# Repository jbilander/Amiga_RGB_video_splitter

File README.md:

# Amiga_RGB_video_splitter
Extend your amiga RGB video signal to two display units - screens, monitors, etc, simultaneously

BOM Rev. C
---------
Reference  | Name/Value   | Package/Footprint | Notes
-|-|-|-|
U1 | THS7374IPWR | TSSOP-14_4.4x5mm_P0.65mm | [THS7374IPWR](https://www.mouser.com/ProductDetail/595-THS7374IPWR)
U2 | 74HCT2G17 | TSOP-6_1.65x3.05mm_P0.95mm | [HCT2G17GV125](https://www.mouser.com/ProductDetail/771-HCT2G17GV125)
U3 | 74HCT2G14 | TSOP-6_1.65x3.05mm_P0.95mm | [HCT2G14GV125](https://www.mouser.com/ProductDetail/771-HCT2G14GV125)
U4 | 74LVC1GX04GV X-TAL DRIVER | TSOP-6_1.65x3.05mm_P0.95mm | [LVC1GX04GV125](https://www.mouser.com/ProductDetail/771-LVC1GX04GV125)
Y1 | 18pF Crystal 28.6363 MHz (NTSC) or 28.375 MHz (PAL) | 3.2 mm x 2.5 mm | [ECS-286.3-18-33-JEM-TR](https://www.mouser.com/ProductDetail/520-286.3-18-33-JEMT) (NTSC)<br /> [ABM8-28.375MHZ-B2-T](https://www.mouser.com/ProductDetail/815-ABM8-28.375-B2-T) (PAL)
J1 | D-SUB DB23| DB23_Female-Connector | [Female 23 PIN DB23](https://www.aliexpress.com/item/1005007020706331.html)
J2 | DSUB-15-HD | HD_Female_Horizontal | [VGA connector](https://www.aliexpress.com/item/1005007383371077.html)
J3 | 9 Pin Mini Din Connector | Right Angle TH Mini Circular DIN Receptacle | [9pin Mini Din](https://www.aliexpress.com/item/1005005737270650.html)
J4 | PJ-320A | DIP 3.5mm Headphone Audio Socket 4Pins Audio interface | [PJ-320A](https://www.aliexpress.com/item/4000661212458.html)
J5 | MSK12D19 | 3Pin Slide Toggle Switch Pitch_2.5mm | [MSK12D19 SMD](https://www.aliexpress.com/item/1005006482584650.html)
J6 | MSK12D19 | 3Pin Slide Toggle Switch Pitch_2.5mm | [MSK12D19 SMD](https://www.aliexpress.com/item/1005006482584650.html)
J7 | Right angle Single-Pin Header | 0.64 mm square pin angled | pin for a flylead back to switchable Agnus pin 41 (or its pad on motherboard, e.g. JP4 on A500 Rev.6A)
JP1 | Solder_Jumper | | Solder Jumper for setting above pin (J7) to either /XCLKEN or OE-signal (inverted /XCLKEN signal).
C1 | 100uF Radial Pitch_2.5mm | Capacitor TH Radial_D5.0mm_P2.50mm | e.g. <br />[ECA-1AM101](https://www.mouser.com/ProductDetail/667-ECE-A0JKA101I) <br />[ECE-A0JKA101I](https://www.mouser.com/ProductDetail/667-ECA-1AM101) <br />Bend down flush to board before soldering
C2-C6 | Ceramic Capacitor 0.1uF = 100nF | 0805 | e.g. [CL21B104KACNFNC](https://www.mouser.com/ProductDetail/187-CL21B104KACNFNC)
C7-C8 | Multilayer Ceramic Capacitors MLCC - 32pF | 0603 | [06031A320FAT2A ](https://www.mouser.com/ProductDetail/581-06031A320FAT2A) for oscillator circuit
RN1-RN2 | 75 Ω RES ARRAY 4 Resistors | 1206 | [CAT16-75R0F4LF](https://www.mouser.com/ProductDetail/652-CAT16-75R0F4LF)
R1 | 330 Ω | 1206 | Series resistor on C-sync line
R2-R4 | 10k Ω | 1206  
R5 | Resistor 2.2M Ω | 0603 | Resistor in oscillator-circuit
R6 | Resistor 1k Ω | 0603 | Resistor in oscillator-circuit
R7 | Resistor 150 Ω | 1206 | Damping resistor for XCLK out to minimize reflections and ringing
Housing | 2 x Plastic Shell Cover | For DB23/DB25 plug | [Aliexpress](https://www.aliexpress.com/item/1005004717091904.html)
4 x PinHeader | PinHeader Board Weight/Level Support | 3-pin 2.54 mm pitch single row | Move the plastic guard to leave ~7.5 mm of pin before soldering in order to hold board in perfect level inside the housing

***

***

If you use jumper-wire from JP1-pin then you bridge it either with the left pad or the right pad depending on your setup:

    1. Motherboard has PAL oscillator and Adapter has NTSC oscillator = bridge JP1-pin with XCLKEN-pad (PAD 1)
    2. Motherboard has NTSC oscillator and Adapter has PAL oscillator = bridge JP1-pin with OE-pad (PAD 3)

Please note, using a jumper-wire is completely optional, You can switch ECS Agnus in Early Startup menu or with software such as Degrader and then you only control the external XLCK-crystal enable or disable via the switch on the adaptor. However it can be more convenient to have both tasks controlled from one single switch, hence connecting a jumper-wire.

***

<br />

Suitable SCART-lead to use with the adapter (originally for the SEGA Mega Drive 2, (Genesis 2) with AC coupling inside) <br />
https://www.aliexpress.com/item/1005007360209844.html

***

<br />

<br />

<br />

<br />
Filter OFF vs. Filter ON<br />
With the THS7374's filter activated you can clearly see that the vertical jailbars are gone (right picture).

***

When ordering from JLCPCB select:

Specify Layer Sequence: Yes

    L1(Top layer):    F_Cu.gbr
    L2(Inner layer1): GND_Cu.gbr
    L3(Inner layer2): VCC_Cu.gbr
    L4(Bottom layer): B_Cu.gbr

Remove Order Number: 

    Specify a location

This will notify JLC where to put the order number, they will replace the "JLCJLCJLCJLC" silkscreen label.

***

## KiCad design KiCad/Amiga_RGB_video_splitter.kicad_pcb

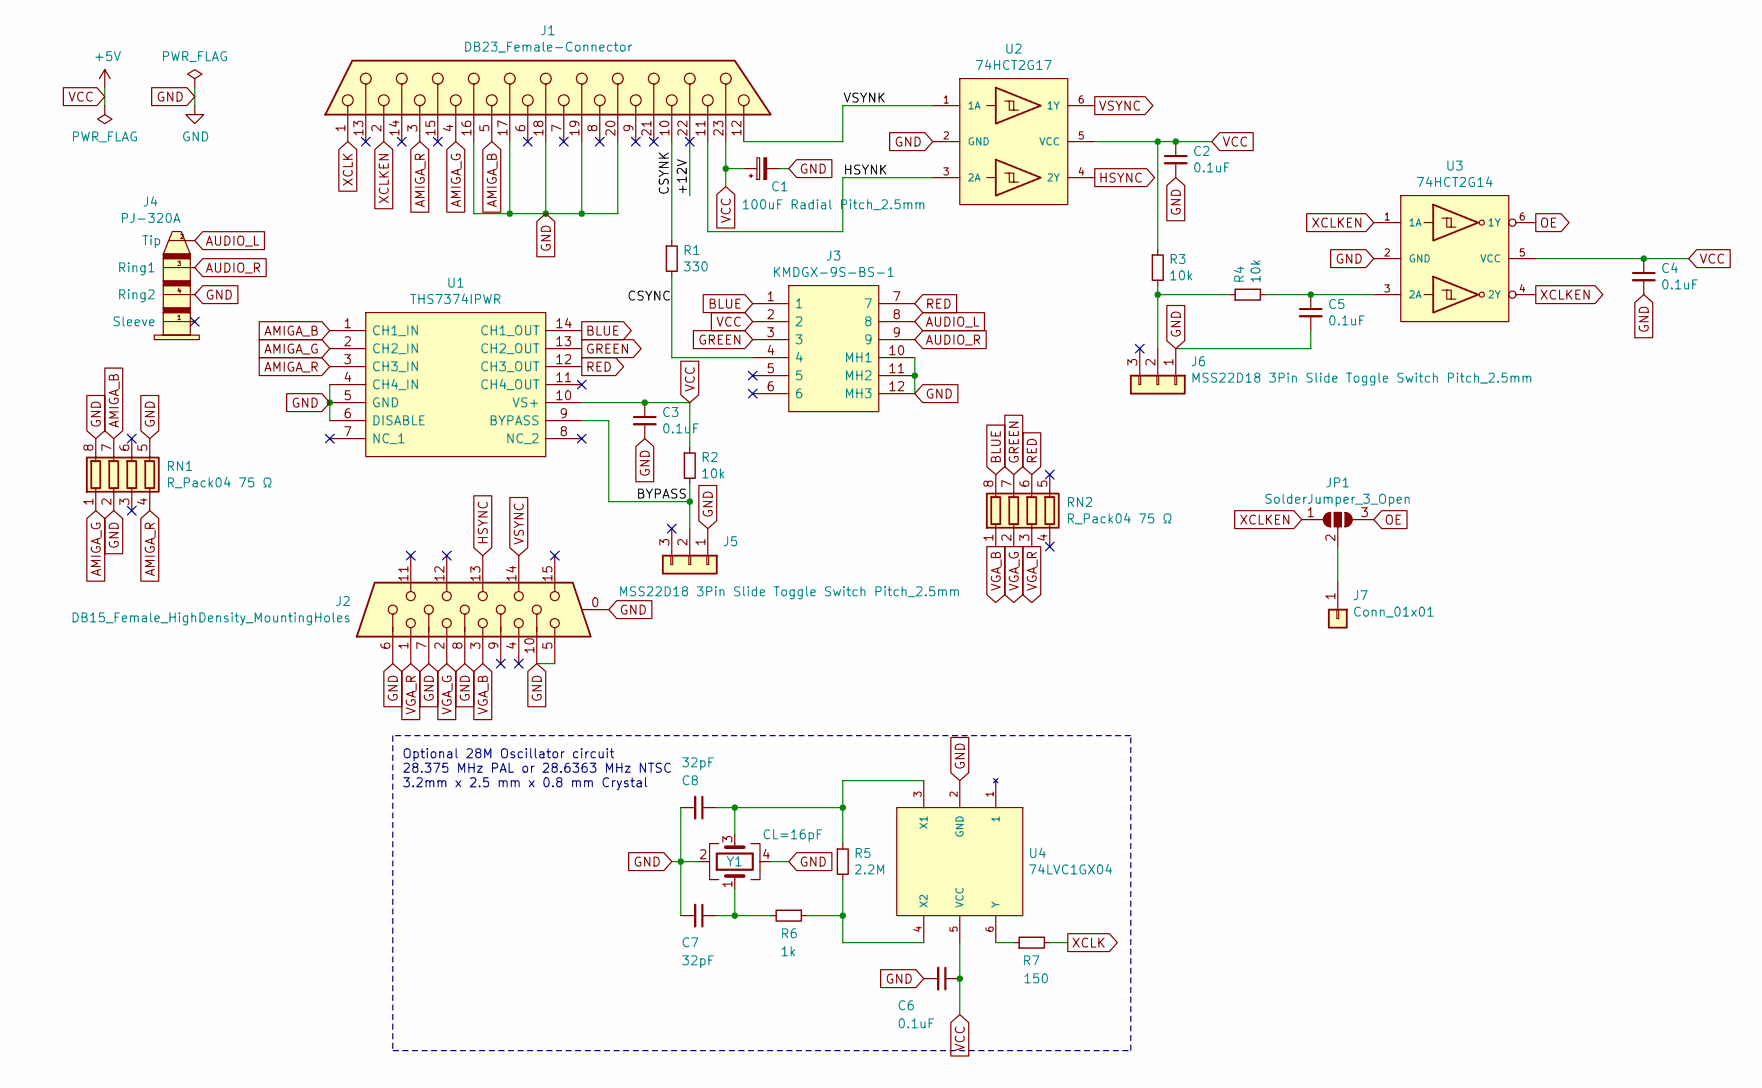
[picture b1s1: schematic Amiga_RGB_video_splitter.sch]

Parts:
C1: 100uF Radial Pitch_2.5mm; CP_Radial_D5.0mm_P2.50mm
C2, C3, C4, C5, C6: 0.1uF; C_0805_2012Metric_Pad1.18x1.45mm_HandSolder
C7, C8: 32pF; C_0603_1608Metric_Pad1.08x0.95mm_HandSolder
J1: DB23_Female-Connector; DSUB-23_Female_EdgeMount_P2.77mm
J2: DB15_Female_HighDensity_MountingHoles; DSUB-15-HD_Female_Horizontal_P2.29x1.98mm_EdgePinOffset3.03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
J3: KMDGX-9S-BS-1; KMDGX9SBS1
J4: PJ-320A
J5, J6: MSS22D18 3Pin Slide Toggle Switch Pitch_2.5mm; PinHeader_1x03_P2.5mm_Vertical
J7: Conn_01x01; PinHeader_1x01_P2.54mm_Vertical
JP1: SolderJumper_3_Open; SolderJumper-3_P1.3mm_Open_RoundedPad1.0x1.5mm_NumberLabels
R1: 330; R_1206_3216Metric_Pad1.30x1.75mm_HandSolder
R2, R3, R4: 10k; R_1206_3216Metric_Pad1.30x1.75mm_HandSolder
R5: 2.2M; R_0603_1608Metric_Pad0.98x0.95mm_HandSolder
R6: 1k; R_0603_1608Metric_Pad0.98x0.95mm_HandSolder
R7: 150; R_1206_3216Metric_Pad1.30x1.75mm_HandSolder
RN1, RN2: R_Pack04 75 Ω; RESCAF80P320X160X60-8N
U1: THS7374IPWR; TSSOP-14_4.4x5mm_P0.65mm
U2: 74HCT2G17; TSOP-6_1.65x3.05mm_P0.95mm
U3: 74HCT2G14; TSOP-6_1.65x3.05mm_P0.95mm
U4: 74LVC1GX04; TSOP-6_1.65x3.05mm_P0.95mm
Y1: CL=16pF; Crystal_SMD_SeikoEpson_FA238-4Pin_3.2x2.5mm

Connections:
/+12V: J1.22
/BYPASS: J5.2, R2.2, U1.9 (BYPASS)
/CSYNC: J3.4, R1.2
/CSYNK: J1.10, R1.1
/HSYNK: J1.11, U2.3 (2A)
/VSYNK: J1.12, U2.1 (1A)
AMIGA_B: J1.5, RN1.7 (R2.2), U1.1 (CH1_IN)
AMIGA_G: J1.4, RN1.1 (R1.1), U1.2 (CH2_IN)
AMIGA_R: J1.3, RN1.4 (R4.1), U1.3 (CH3_IN)
AUDIO_L: J3.8, J4.2 (Tip)
AUDIO_R: J3.9, J4.3 (Ring1)
BLUE: J3.1, RN2.8 (R1.2), U1.14 (CH1_OUT)
GND: C1.2, C2.2, C3.2, C4.2, C5.2, C6.2, C7.2, C8.2, J1.16, J1.17, J1.18, J1.19, J1.20, J2.0, J2.5, J2.6, J2.7, J2.8, J2.10, J3.10 (MH1), J3.11 (MH2), J3.12 (MH3), J4.4 (Ring2), J5.1, J6.1, RN1.2 (R2.1), RN1.5 (R4.2), RN1.8 (R1.2), U1.4 (CH4_IN), U1.5 (GND), U1.6 (DISABLE), U2.2 (GND), U3.2 (GND), U4.2 (GND), Y1.2, Y1.4
GREEN: J3.3, RN2.7 (R2.2), U1.13 (CH2_OUT)
HSYNC: J2.13, U2.4 (2Y)
unnamed: C5.1, R4.2, U3.3 (2A)
unnamed: C7.1, R6.2, Y1.1
unnamed: C8.1, R5.1, U4.3 (X1), Y1.3
unnamed: J6.2, R3.2, R4.1
unnamed: J7.1, JP1.2 (C)
unnamed: R5.2, R6.1, U4.4 (X2)
unnamed: R7.1, U4.6 (Y)
OE: JP1.3 (B), U3.6 (1Y)
RED: J3.7, RN2.6 (R3.2), U1.12 (CH3_OUT)
VCC: C1.1, C2.1, C3.1, C4.1, C6.1, J1.23, J3.2, R2.1, R3.1, U1.10 (VS+), U2.5 (VCC), U3.5 (VCC), U4.5 (VCC)
VGA_B: J2.3, RN2.1 (R1.1)
VGA_G: J2.2, RN2.2 (R2.1)
VGA_R: J2.1, RN2.3 (R3.1)
VSYNC: J2.14, U2.6 (1Y)
XCLK: J1.1, R7.2
XCLKEN: J1.2, JP1.1 (A), U3.1 (1A), U3.4 (2Y)

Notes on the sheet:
Optional 28M Oscillator circuit 28.375 MHz PAL or 28.6363 MHz NTSC 3.2mm x 2.5 mm x 0.8 mm Crystal

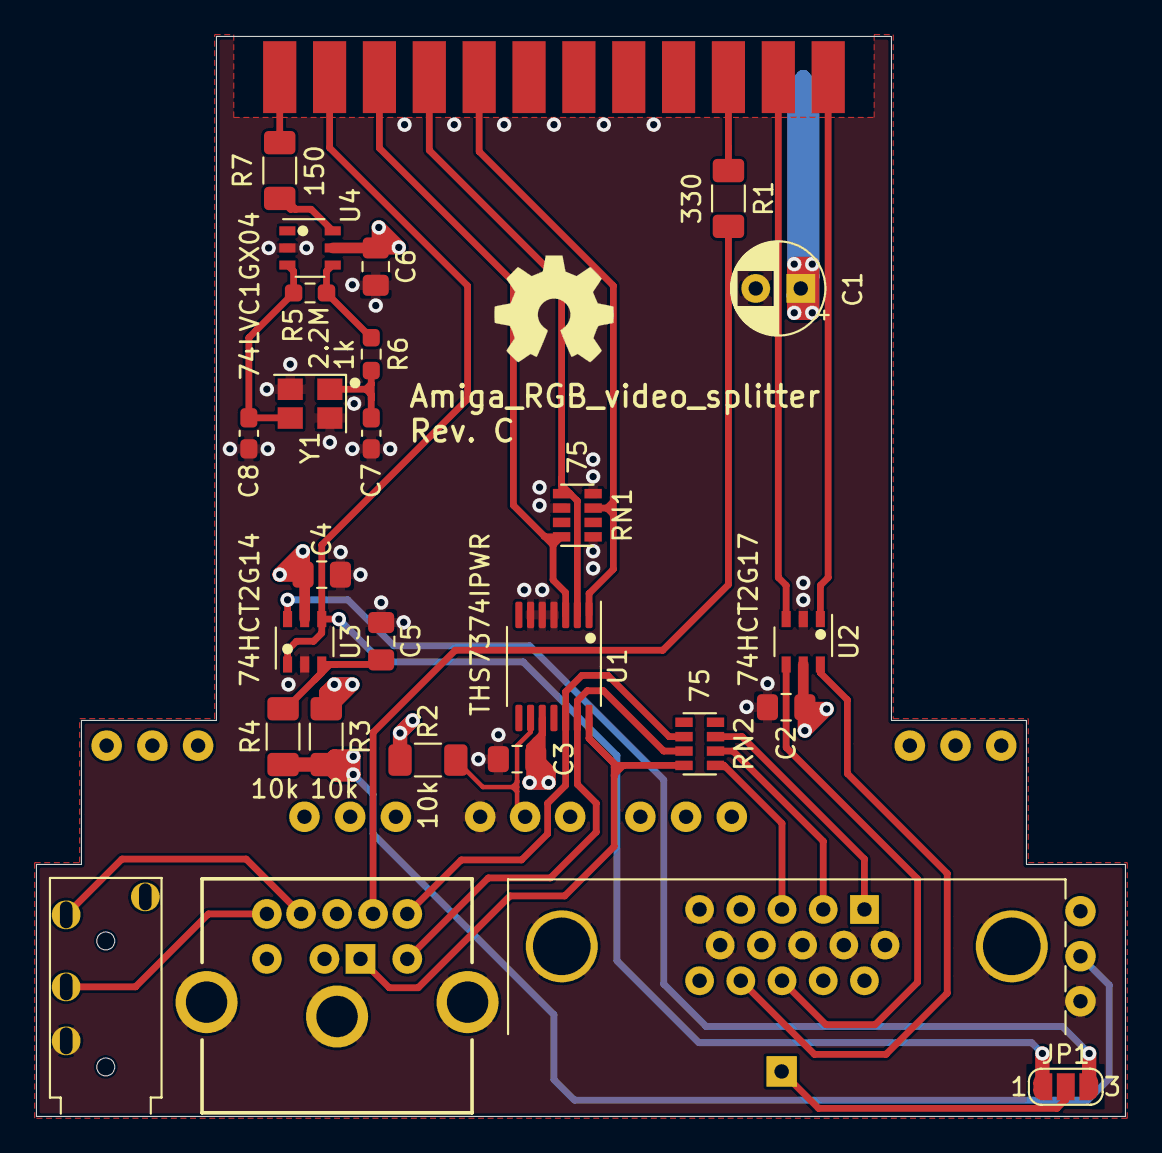
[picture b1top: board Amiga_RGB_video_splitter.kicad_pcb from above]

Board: 4 copper layers, 60.5 x 60.0 mm, 30 parts (1 on the bottom side), 30 nets.

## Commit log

2025-05-19 Create LICENSE
2025-05-19 Add footprint
2025-05-19 Add kicad files
2025-05-19 Add symbol and place footprint for Connector_DB15_Female_HighDensity_MountingHoles
2025-05-19 Add Mini DIN 9 position receptacle connector
2025-05-19 Add 3D-model of Mini DIN 9 position receptacle connector
2025-05-19 Change 3D-model for Mini DIN 9 connector to KMDGX-9S-BS-1_A1.stp
2025-05-23 Add symbol for PJ-320A
2025-05-23 Add footprint for PJ-320A
2025-05-23 Add 3D-model of PJ-320A
2025-05-23 Add a PJ-320A stereo input connector to the design
2025-05-23 Add symbol for THS7374IPWR
2025-05-23 Add THS7374IPWR to the design and temporary routing
2025-05-23 Add footprint for THS7374IPWR
2025-05-23 Add capacitor and route VCC to pin 10 on U1, add resistor R1 to Csync line
2025-05-23 Add 75 Ω termination for RGB lines with resistor pack RN1
2025-05-23 Add series resistor for VGA RGB lines with resistor pack RN2
2025-05-26 Add 74HCT2G17 symbol to library
2025-05-26 Add U2 (74HCT2G17) in TSOP-6 to the design for V-sync and H-sync buffering
2025-05-26 Silkscreen fix on footprint
2025-05-26 Change C1 to C2 and C2 to C3 and adding resistor Ohm values on silkscreen
2025-05-26 Add polarized TH-capacitor C1 100uF Radial pitch 2.5 mm
2025-05-28 Add 10k pull-up resistor R2 for BYPASS signal going to MSS22D18 3-Pin slide toggle switch
2025-05-28 Add footprint for MSS22D18 3-Pin slide toggle switch
2025-05-28 Add 3D-model for resistor pack
2025-05-28 Add 3D-model for MSS22D18 3-Pin slide toggle switch
2025-05-28 Add 74HCT2G14 and 74LVC1GX04 symbols to library
2025-05-28 Add U3 (74HCT2G14) and R3,R4,C4,C5 to the design
2025-05-28 Placement of R3,R4,C4,C5 and routing of U3 circuit
2025-05-29 Add U4 (74LVC1GX04) to the design
2025-05-29 Placement and routing of U4 (74LVC1GX04)
2025-05-29 Add Y1 crystal to the design
2025-05-30 Add capacitor C7 and C8, and some silkscreen fixes
2025-05-30 Add solder jumper JP1 to the design and route signals XCLKEN and OE to it
2025-05-30 Update holes to 0.8 mm in diameter
2025-05-30 Add four PinHeader_1x03_P2.54mm for support structure, fix of edge cuts for better fit plastic shells
2025-05-30 Add 3D-model of DB23 connector
2025-05-30 Small silkscreen fix
2025-05-31 silkscreen fix
2025-05-31 Update plot params
2025-08-02 Update footprints
2025-08-02 Fix placement of support pinheaders and RN2, some rerouting and silkscreen fixes, bump revision to Rev B
2025-08-09 Relocate the PAL/NTSC 3Pin Slide Toggle Switch
2025-08-09 Silkscreen fix on VGA connector footprint
2025-08-15 Add schematic pdf
2025-08-17 Add images
2026-02-15 Add damping 150 Ohm series resistor on XCLK out, bump to Rev. C
2026-02-15 Add schematic

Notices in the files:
KiCad/Amiga_RGB_video_splitter.kicad_pcb:
(C) 2025
